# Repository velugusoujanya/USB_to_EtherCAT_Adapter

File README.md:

<div align="center" style="border: 2px solid #ccc; padding: 20px; border-radius: 12px; width: 80%; margin: auto; box-shadow: 0 0 10px rgba(0,0,0,0.15);">

  <h1 align="center" style="font-family: Arial; font-weight: 600; margin-top: 15px;">SURE ProEd (formerly SURE Trust) 
      </h1>
<h2 style="color: #2b6cb0; font-family: Arial;">Skill Upgradation for Rural youth Empowerment Trust</h2>
</div>

<hr style="border: 0; border-top: 1px solid #ccc; width: 80%;" />

<div style="padding: 20px; border: 2px solid #ddd; border-radius: 12px; width: 90%; margin: auto; background: #fafafa; font-family: Arial;">

<h2 style = "color:#333;"> Student Details </h2>
<div align = "left" style ="margin: 20px; font-size: 16px;">
    <p><strong>Name:</strong> Velugu Soujanya </p>
    <p><strong>Email ID:</strong> soujanya.velugu@gmail.com </p>
    <p><strong>College Name:</strong> Vasavi College of Engineering </p>
    <p><strong>Branch/Specialization :</strong> Communication Engineering & Signal Processing</p>
    <p><strong>College ID:</strong> 160212744111 </p>
</div>

<hr style="border: 0; border-top: 1px solid #ccc; width: 80%;" />

<h2 style="color:#333;"> Course Details </h2>
<div align="left" style="margin: 20px; font-size: 16px;">
    <p><strong>Course Opted:</strong> PCB DESIGN </p>
    <p><strong>Instructor Name:</strong> Mounika </p>
</div>
<div align="left" style="margin: 20px; font-size: 16px;">
    <p><strong>Duration:</strong> six months </p>

<hr style="border: 0; border-top: 1px solid #ccc; width: 80%;" />

<h2 style="color:#333;"> Trainer Details </h2>
<div align="left" style="margin: 20px; font-size: 16px;">

<p><strong>Trainer Name:</strong> Paremesh Kumar </p>
<p><strong>Trainer Email ID:</strong> parameshkumar432@gmail.com </p>
<p><strong>Trainer Designation:</strong> Hardware Design Engineer </p>

<hr style="border: 0; border-top: 1px solid #ccc; width: 80%;" />

## **Table of Contents**
- [Course Learning](#course-learning-to-be-edited-by-student)
- [Projects Completed](#projects-completed)
- [Project Introduction](#project-introduction)
- [Technologies Used](#technologies-used)
- [Roles and Responsibilities](#roles-and-responsibilities)
- [Project Report](#project-report)
- [Learnings from LST & SST](#learnings-from-lst--sst)
- [Community Services](#community-services)
- [Certificate](#certificate)
- [Acknowledgments](#acknowledgments)

<hr style="border: 0; border-top: 1px solid #ccc; width: 80%;" />

## Overall Learning 

During this course,I learned how to design PCB in KiCad.
I gained hands-on experience in high speed hardware shematic design and PCB layout using KiCad by developing the USB to EtherCAT Adapter Board,and strengthened my skills in problem-solving, teamwork, documentation, and delivering real-world project solutions.

<h2 style="color:#333;"> Projects Completed </h2>
<div align="left" style="margin: 20px; font-size: 16px;">

<p><strong><a href="#project1">Project 1:</a></strong> USB to EtherCAT Adapter Board V.1.0 </p>

</div>

<!-- Project 1 -->
<h3 id="project1">Project 1: USB to EtherCAT Adapter Board V.1.0 </h3>
<p>
  This project involved designing and developing complete USB to EtherCAT Adapter Board using KiCad.It focused on schematic capture,component selection,PCB layout, and generating fabrication-ready manufacturing outputs including gerber files,drill files, and detailed Bill of Materials(BOM) for production.
</p>
<p>
  <a href="https://github.com/velugusoujanya/USB_to_EtherCAT_Adapter/blob/64acc3698a79dc94cf15804da77aeb8a2aae306a/Project%20Report.pdf" target="_blank"><strong>→ View Full Project Report</strong></a>
</p>

<hr style="height:1px; border-top:1px solid #ccc; width:80%;" />

## **References**

- [Google](https://google.com)
- [Gemini](https://gemini.google.com)

## **Learnings from LST and SST**

LST and SST sessions significantly improved my emotional intelligence,slf-dicipline, and interpersonal skills. They helped me build strong ethical values,manage stress effectively,and communicate with greater clarity and confidence in both personal and professional environments.

---

## **Community Services**

During my internship period, I actively participated in multiple community-oriented intiatives aimed at promoting social welfare
,environmental sustainability. These activities provided a valuable opportunity to give back to society while forecasting teamwork,empathy,and civic sustainability.
### **Activities Involved**
  
 Hayathnagar, Hyderabad
- **Tree Plantation Drive** – Participated by planting trees and contributing to environmental improvement.

  Amrutha oldage home, Hayathnagar
- **Helping Elder Citizens** – Supported the health and well-being of 10 senior citizens  at Sharada Old Age Home by providing nutritious fruits,offering emotional companionship,and helping reduce feelings of isolation.

I felt very happy after coming from there,by seeing me they are feeling like theire relatives came to help them.I slept very happily that day.Thanks to suretrust for making me to feel happy.

### **Impact / Contribution**

- Actively participated in promoting a greener and cleaner surroundings.
- Offered personal assistance to elder citizens, strengthening community bonds.
- Improved skills in communication, coordination, and social responsibility.

### **Photos**

<!-- add your photos below -->
<!-- change url below with your image urls (inside  src='')-->

<div align="center">

</div>

---

## **Certificate**

The internship certificate serves as an official acknowledgment of the successful completion of my training period. It will be issued by the organization upon fulfilling all required tasks and meeting the performance expectations of the program. The certificate validates the skills, experience, and contributions made during the internship.

<!-- add your certificate image url below (inside src='')-->

---

## **Acknowledgments**
A heartfelt thank you to Prof. Radhakumari Challa Mam and my mentor Mr. Paramesh Kumar Sir for supporting my development both as a professional and a citizen during my PCB Design journey. 
<!-- you can add Acknowledgments over here in same syntax as below . eg trainer name , company name , role etc -->
-[Mr.Paramesh Kumar](https://www.linkedin.com/in/paramesh-kumar-c-ab6b65244/) , Hardware Design Engineer - [Wakefit innovations]

- [Prof. Radhakumari Challa](https://www.linkedin.com/in/prof-radhakumari-challa-a3850219b) , Executive Director and Founder - [SURE Trust](https://www.suretrustforruralyouth.com/)

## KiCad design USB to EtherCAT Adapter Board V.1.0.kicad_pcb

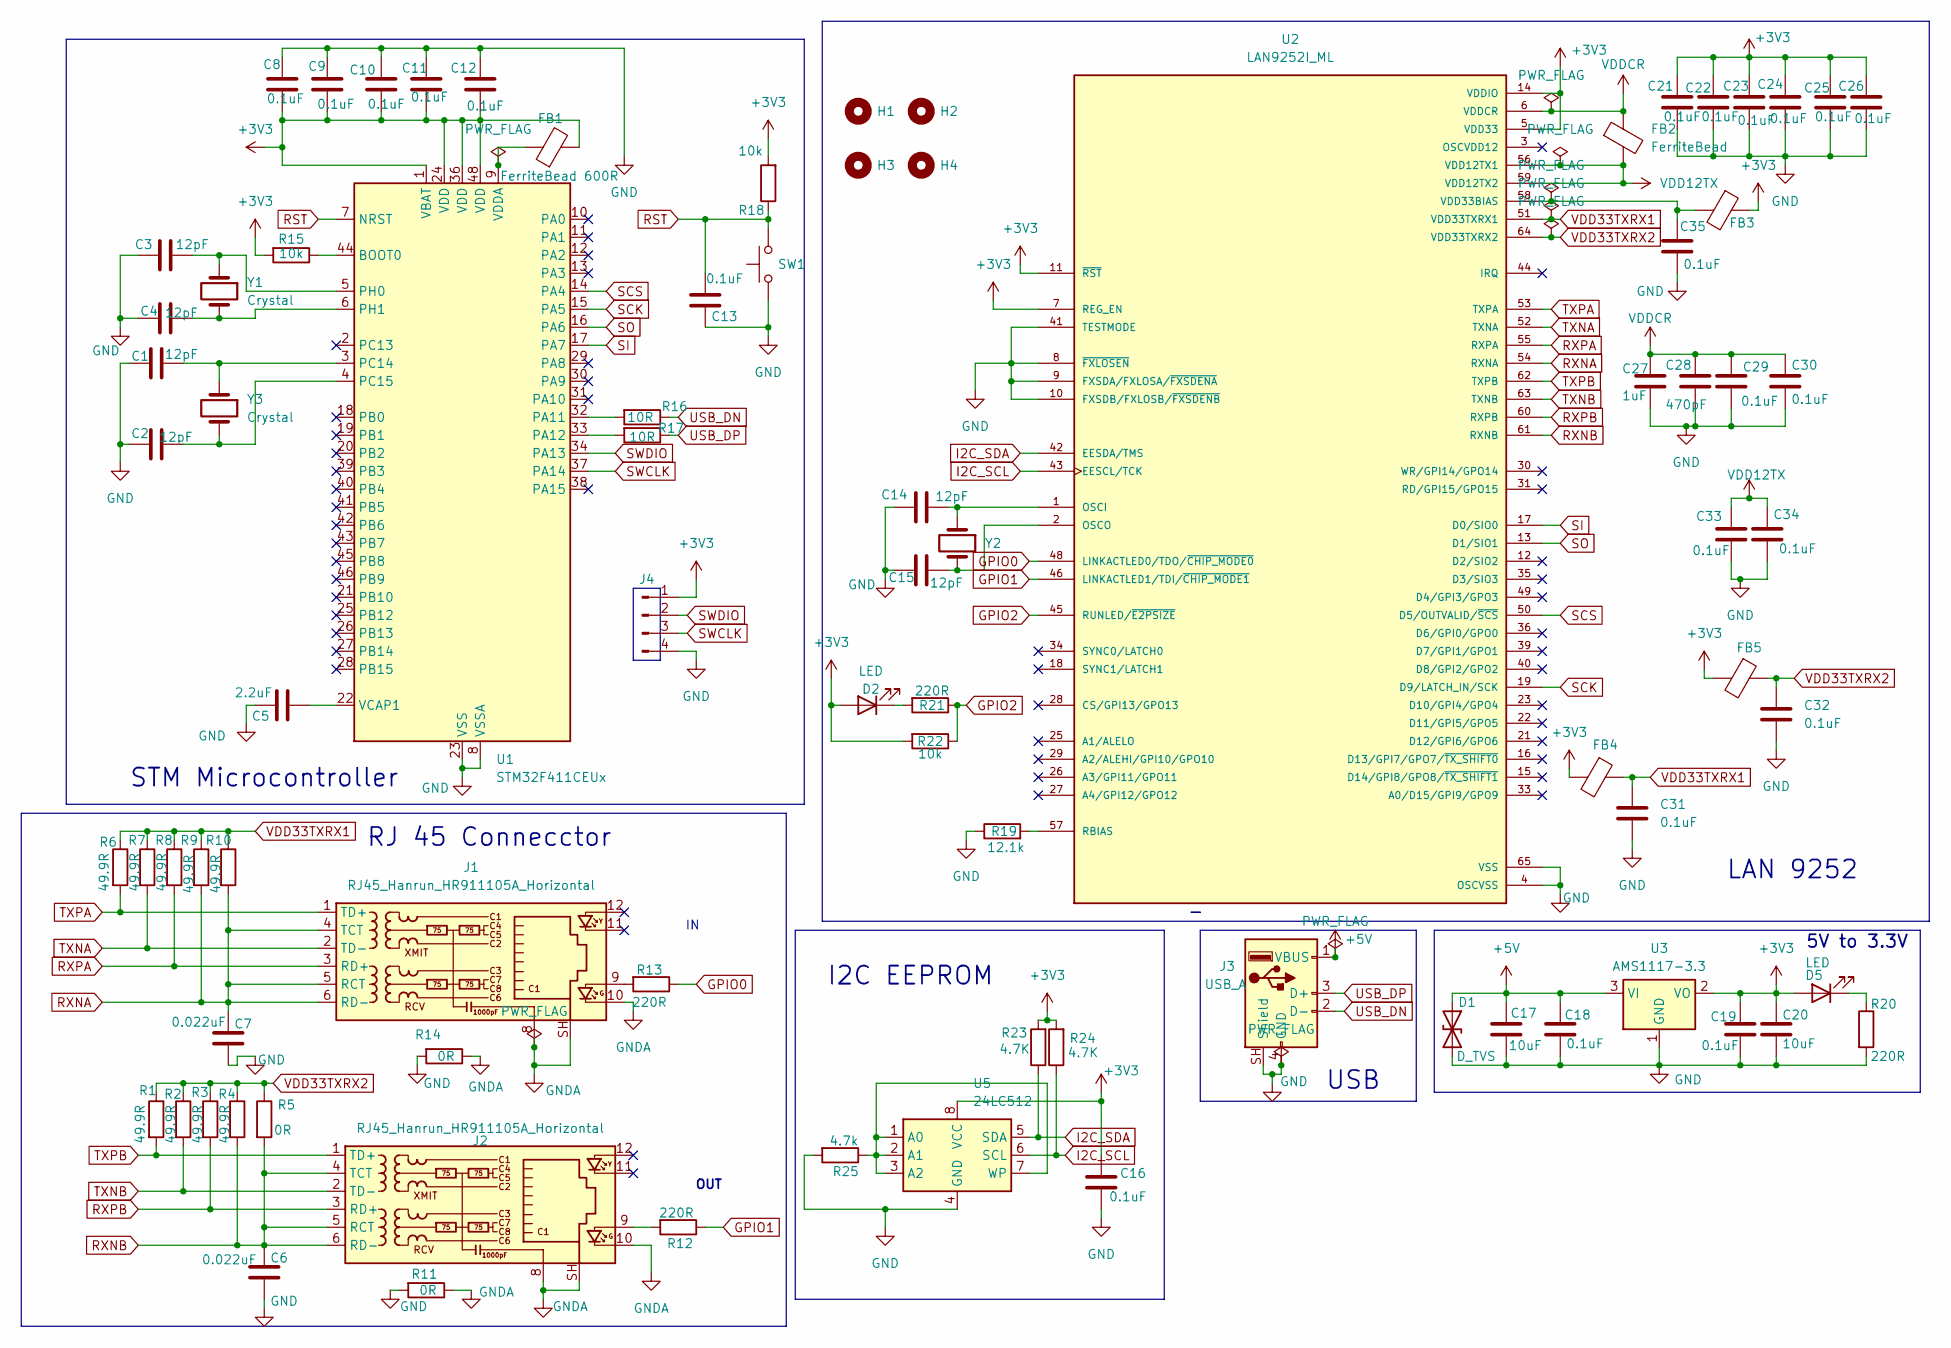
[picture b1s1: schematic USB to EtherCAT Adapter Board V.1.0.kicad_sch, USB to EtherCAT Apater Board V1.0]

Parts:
C1, C2, C3, C4, C14, C15: 12pF; C_0805_2012Metric
C5: 2.2uF; C_0805_2012Metric
C6, C7: 0.022uF; C_0805_2012Metric
C8, C9, C10, C11, C12, C13, C16, C18, C19, C21, C22, C23, C24, C25, C26, C29, C30, C31, C32, C33, C34, C35: 0.1uF; C_0805_2012Metric
C17, C20: 10uF; C_0805_2012Metric
C27: 1uF; C_0805_2012Metric
C28: 470pF; C_0805_2012Metric
D1: D_TVS; D_0805_2012Metric
D2, D5: LED; LED_0805_2012Metric
FB1: FerriteBead 600R; L_0805_2012Metric
FB2, FB3, FB4, FB5: FerriteBead; L_0805_2012Metric
H1, H2, H3, H4: MountingHole; MountingHole_2.1mm
J1, J2: RJ45_Hanrun_HR911105A_Horizontal
J3: USB_A; USB_A_Molex_67643_Horizontal
J4: Conn_01x04_Pin; PinHeader_1x04_P2.54mm_Vertical
R1, R2, R3, R4, R6, R7, R8, R9, R10: 49.9R; R_0805_2012Metric
R5, R11, R14: 0R; R_0805_2012Metric
R12, R13, R20, R21: 220R; R_0805_2012Metric
R15, R18, R22: 10k; R_0805_2012Metric
R16, R17: 10R; R_0805_2012Metric
R19: 12.1k; R_0805_2012Metric
R23, R24: 4.7K; R_0805_2012Metric
R25: 4.7k; R_0805_2012Metric
SW1: SW_Push; SW_Push_SPST_NO_Alps_SKRK
U1: STM32F411CEUx; QFN-48-1EP_7x7mm_P0.5mm_EP5.6x5.6mm
U2: LAN9252I_ML; QFP50P1200X1200X120-65N; PARTREV DS00001909B
U3: AMS1117-3.3; SOT-223-3_TabPin2
U5: 24LC512; SOIC-8_3.9x4.9mm_P1.27mm
Y1, Y2: Crystal; Crystal_SMD_HC49-SD
Y3: Crystal; Crystal_SMD_3215-2Pin_3.2x1.5mm

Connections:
+3V3: C8.1, C9.1, C10.1, C11.1, C12.1, C16.1, C19.1, C20.1, C21.1, C22.1, C23.1, C24.1, C25.1, C26.1, D2.2 (A), D5.2 (A), FB1.2, FB3.1, FB4.2, FB5.2, J4.1, R15.2, R18.2, R22.2, R23.2, R24.2, U1.1 (VBAT), U1.24 (VDD), U1.36 (VDD), U1.48 (VDD), U2.5 (VDD33), U2.7 (REG_EN), U2.11 (~RST), U2.14 (VDDIO), U2.20 (VDDIO), U2.32 (VDDIO), U2.37 (VDDIO), U2.47 (VDDIO), U3.2 (VO), U5.8 (VCC)
+5V: C17.1, C18.1, D1.1 (A1), J3.1 (VBUS), U3.3 (VI)
GND: C1.2, C2.2, C3.2, C4.2, C5.2, C6.1, C7.1, C8.2, C9.2, C10.2, C11.2, C12.2, C13.1, C14.1, C15.1, C16.2, C17.2, C18.2, C19.2, C20.2, C21.2, C22.2, C23.2, C24.2, C25.2, C26.2, C27.2, C28.2, C29.2, C30.2, C31.2, C32.2, C33.2, C34.2, C35.2, D1.2 (A2), J3.4 (GND), J3.SH (Shield), J4.4, R11.2, R14.2, R19.1, R20.2, R25.2, SW1.1, U1.8 (VSSA), U1.23 (VSS), U1.35 (VSS), U1.47 (VSS), U1.49 (VSS), U2.4 (OSCVSS), U2.8 (~FXLOSEN), U2.9 (FXSDA/FXLOSA/~FXSDENA), U2.10 (FXSDB/FXLOSB/~FXSDENB), U2.41 (TESTMODE), U2.65 (VSS), U3.1 (GND), U5.4 (GND)
GNDA: J1.8, J1.10, J1.SH, J2.8, J2.10, J2.SH, R11.1, R14.1
GPIO0: R13.1, U2.48 (LINKACTLED0/TDO/~CHIP_MODE0)
GPIO1: R12.1, U2.46 (LINKACTLED1/TDI/~CHIP_MODE1)
GPIO2: R21.1, R22.1, U2.45 (RUNLED/~E2PSIZE)
I2C_SCL: R24.1, U2.43 (EESCL/TCK), U5.6 (SCL)
I2C_SDA: R23.1, U2.42 (EESDA/TMS), U5.5 (SDA)
unnamed: D2.1 (K), R21.2
unnamed: D5.1 (K), R20.1
unnamed: J1.9, R13.2
unnamed: J2.9, R12.2
unnamed: R15.1, U1.44 (BOOT0)
unnamed: R16.2, U1.32 (PA11)
unnamed: R17.2, U1.33 (PA12)
unnamed: C1.1, U1.3 (PC14), Y3.1
unnamed: C2.1, U1.4 (PC15), Y3.2
unnamed: C3.1, U1.5 (PH0), Y1.1
unnamed: C4.1, U1.6 (PH1), Y1.2
unnamed: C5.1, U1.22 (VCAP1)
unnamed: FB1.1, U1.9 (VDDA)
unnamed: C14.2, U2.1 (OSCI), Y2.1
unnamed: C15.2, U2.2 (OSCO), Y2.2
unnamed: R19.2, U2.57 (RBIAS)
unnamed: C35.1, FB3.2, U2.58 (VDD33BIAS)
unnamed: R25.1, U5.1 (A0), U5.2 (A1), U5.3 (A2), U5.7 (WP)
RST: C13.2, R18.1, SW1.2, U1.7 (NRST)
RXNA: C7.2, J1.4 (TCT), J1.5 (RCT), J1.6 (RD-), R9.2, R10.2, U2.54 (RXNA)
RXNB: C6.2, J2.4 (TCT), J2.5 (RCT), J2.6 (RD-), R4.2, R5.2, U2.61 (RXNB)
RXPA: J1.3 (RD+), R8.2, U2.55 (RXPA)
RXPB: J2.3 (RD+), R3.2, U2.60 (RXPB)
SCK: U1.15 (PA5), U2.19 (D9/LATCH_IN/SCK)
SCS: U1.14 (PA4), U2.50 (D5/OUTVALID/~SCS)
SI: U1.17 (PA7), U2.17 (D0/SIO0)
SO: U1.16 (PA6), U2.13 (D1/SIO1)
SWCLK: J4.3, U1.37 (PA14)
SWDIO: J4.2, U1.34 (PA13)
TXNA: J1.2 (TD-), R7.2, U2.52 (TXNA)
TXNB: J2.2 (TD-), R2.2, U2.63 (TXNB)
TXPA: J1.1 (TD+), R6.2, U2.53 (TXPA)
TXPB: J2.1 (TD+), R1.2, U2.62 (TXPB)
USB_DN: J3.2 (D-), R16.1
USB_DP: J3.3 (D+), R17.1
VDD12TX: C33.1, C34.1, FB2.2, U2.56 (VDD12TX1), U2.59 (VDD12TX2)
VDD33TXRX1: C31.1, FB4.1, R6.1, R7.1, R8.1, R9.1, R10.1, U2.51 (VDD33TXRX1)
VDD33TXRX2: C32.1, FB5.1, R1.1, R2.1, R3.1, R4.1, R5.1, U2.64 (VDD33TXRX2)
VDDCR: C27.1, C28.1, C29.1, C30.1, FB2.1, U2.6 (VDDCR), U2.24 (VDDCR), U2.38 (VDDCR)

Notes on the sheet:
I2C EEPROM
OUT
RJ 45 Connecctor
LAN 9252
STM Microcontroller
USB
5V to 3.3V

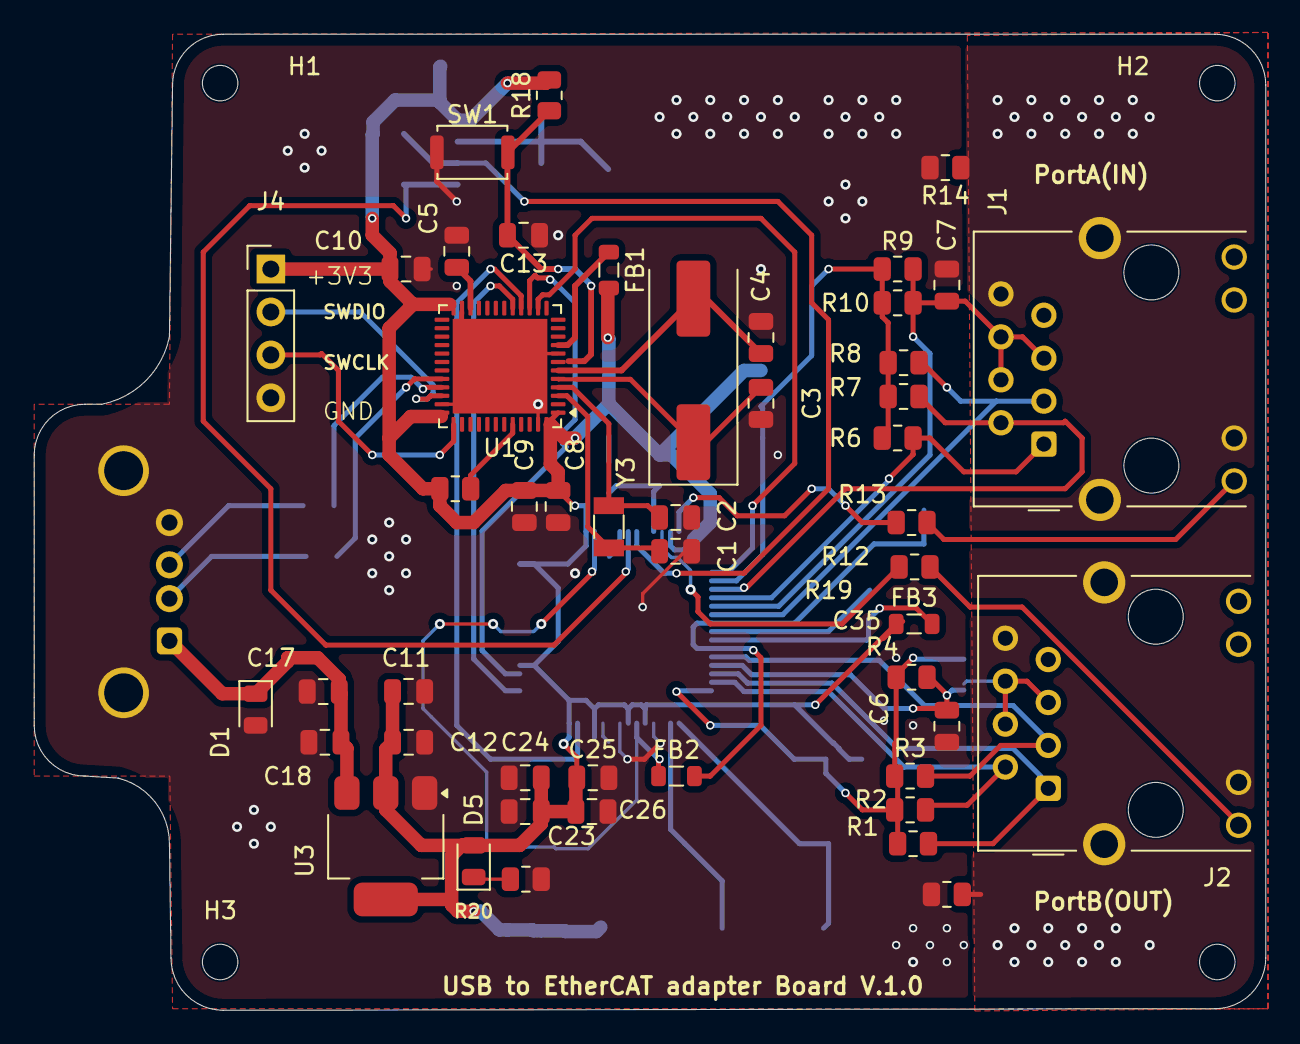
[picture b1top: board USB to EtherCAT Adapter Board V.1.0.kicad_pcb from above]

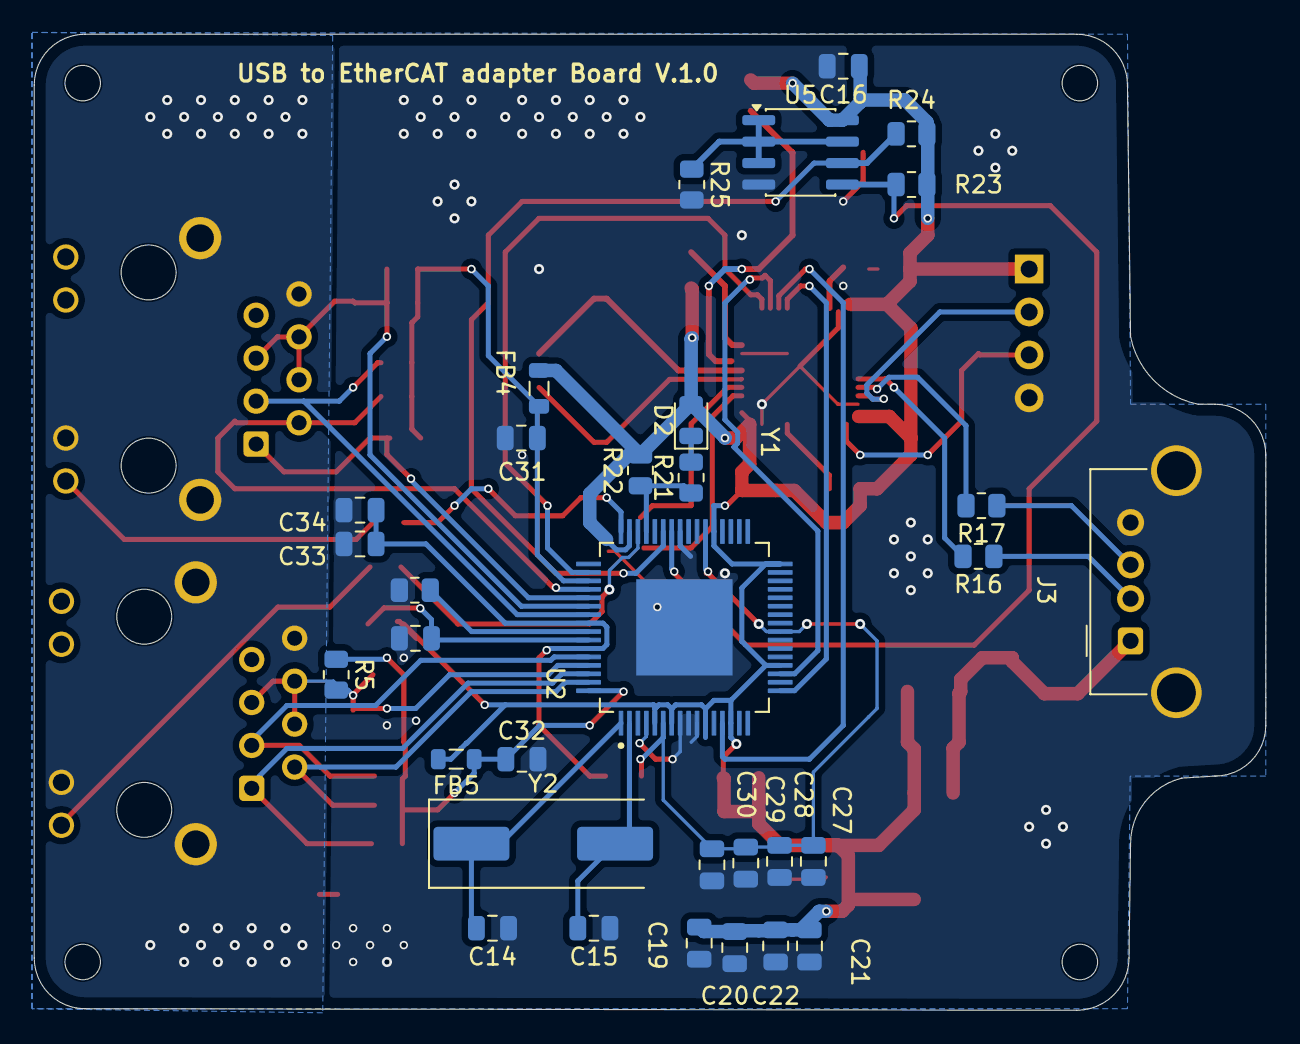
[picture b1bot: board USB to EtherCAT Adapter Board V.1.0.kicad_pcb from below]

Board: 2 copper layers, 72.9 x 57.8 mm, 84 parts (32 on the bottom side), 48 nets.

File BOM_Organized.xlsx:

Reference | Value | Datasheet | Footprint | Qty | DNP
U1 | STM32F411CEUx | https://www.st.com/resource/en/datasheet/stm32f411ce.pdf | Package_DFN_QFN:QFN-48-1EP_7x7mm_P0.5mm_EP5.6x5.6mm | 1
U2 | LAN9252I_ML |  | LAN9252_PT:QFP50P1200X1200X120-65N | 1
U3 | AMS1117-3.3 | http://www.advanced-monolithic.com/pdf/ds1117.pdf | Package_TO_SOT_SMD:SOT-223-3_TabPin2 | 1
U5 | 24LC512 | http://ww1.microchip.com/downloads/en/DeviceDoc/21754M.pdf | Package_SO:SOIC-8_3.9x4.9mm_P1.27mm | 1
J1,J2 | RJ45_Hanrun_HR911105A_Horizontal | https://datasheet.lcsc.com/lcsc/1811141815_HANRUN-Zhongshan-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 | Connector_RJ:RJ45_Hanrun_HR911105A_Horizontal | 2
J3 | USB_A |  | Connector_USB:USB_A_Molex_67643_Horizontal | 1
J4 | Conn_01x04_Pin |  | Connector_PinHeader_2.54mm:PinHeader_1x04_P2.54mm_Vertical | 1
R1,R2,R3,R4,R6,R7,R8,R9,R10 | 49.9R |  | Resistor_SMD:R_0805_2012Metric | 9
R12,R13,R20,R21 | 220R |  | Resistor_SMD:R_0805_2012Metric | 4
R15,R18,R22 | 10k |  | Resistor_SMD:R_0805_2012Metric | 3
R16,R17 | 10R |  | Resistor_SMD:R_0805_2012Metric | 2
R19 | 12.1k |  | Resistor_SMD:R_0805_2012Metric | 1
R23,R24 | 4.7K |  | Resistor_SMD:R_0805_2012Metric | 2
R25 | 4.7k |  | Resistor_SMD:R_0805_2012Metric | 1
R5,R11,R14 | 0R |  | Resistor_SMD:R_0805_2012Metric | 3
C1,C2,C3,C4,C14,C15 | 12pF |  | Capacitor_SMD:C_0805_2012Metric | 6
C17,C20 | 10uF |  | Capacitor_SMD:C_0805_2012Metric | 2
C27 | 1uF |  | Capacitor_SMD:C_0805_2012Metric | 1
C28 | 470pF |  | Capacitor_SMD:C_0805_2012Metric | 1
C5 | 2.2uF |  | Capacitor_SMD:C_0805_2012Metric | 1
C6,C7 | 0.022uF |  | Capacitor_SMD:C_0805_2012Metric | 2
C8,C9,C10,C11,C12,C13,C16,C18,C19,C21,C22,C23,C24,C25,C26,C29,C30,C31,C32,C33,C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 | 0.1uF |  | Capacitor_SMD:C_0805_2012Metric | 22
D1 | D_TVS |  | Diode_SMD:D_0805_2012Metric | 1
D2,D5 | LED |  | LED_SMD:LED_0805_2012Metric | 2
FB1 | FerriteBead 600R |  | Inductor_SMD:L_0805_2012Metric | 1
FB2,FB3,FB4,FB5 | FerriteBead |  | Inductor_SMD:L_0805_2012Metric | 4
Y1,Y2,Y3 | Crystal |  | Crystal:Crystal_SMD_3215-2Pin_3.2x1.5mm,Crystal:Crystal_SMD_HC49-SD | 3
SW1 | SW_Push |  | Button_Switch_SMD:SW_Push_SPST_NO_Alps_SKRK | 1
